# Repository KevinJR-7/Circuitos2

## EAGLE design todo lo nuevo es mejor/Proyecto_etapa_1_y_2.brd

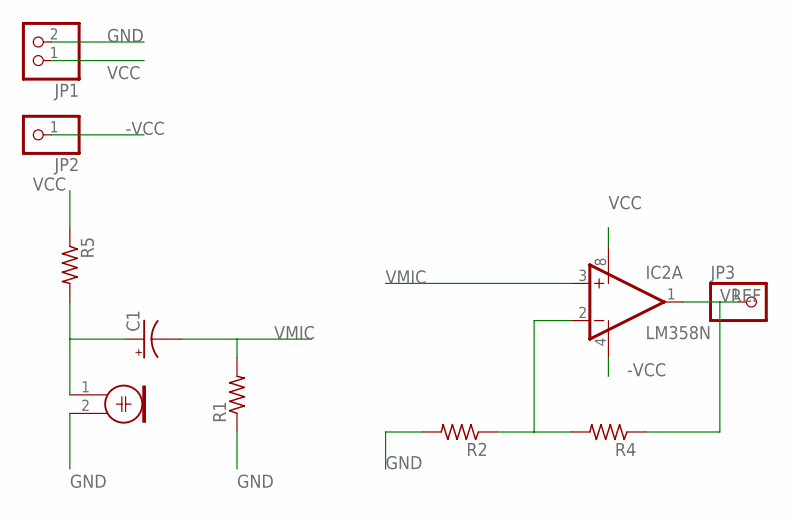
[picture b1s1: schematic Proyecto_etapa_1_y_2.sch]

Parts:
C1: CPOL-USE2.5-6; E2,5-6
IC2: LM358N; DIL08
JP1: PINHD-1X2; 1X02
JP2, JP3: PINHD-1X1; 1X01
M2: ELECTRET_MICROPHON-F6050AP; F6050AP
R1, R2, R4, R5: R-US_0207/10; 0207/10

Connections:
-VCC: IC2.4 (V-), JP2.1
GND: JP1.2, M2.2, R1.1, R2.2
unnamed: C1.+, M2.1, R5.2
unnamed: IC2.2 (-IN), R2.1, R4.2
VCC: IC2.8 (V+), JP1.1, R5.1
VMIC: C1.-, IC2.3 (+IN), R1.2
VREF: IC2.1 (OUT), JP3.1, R4.1

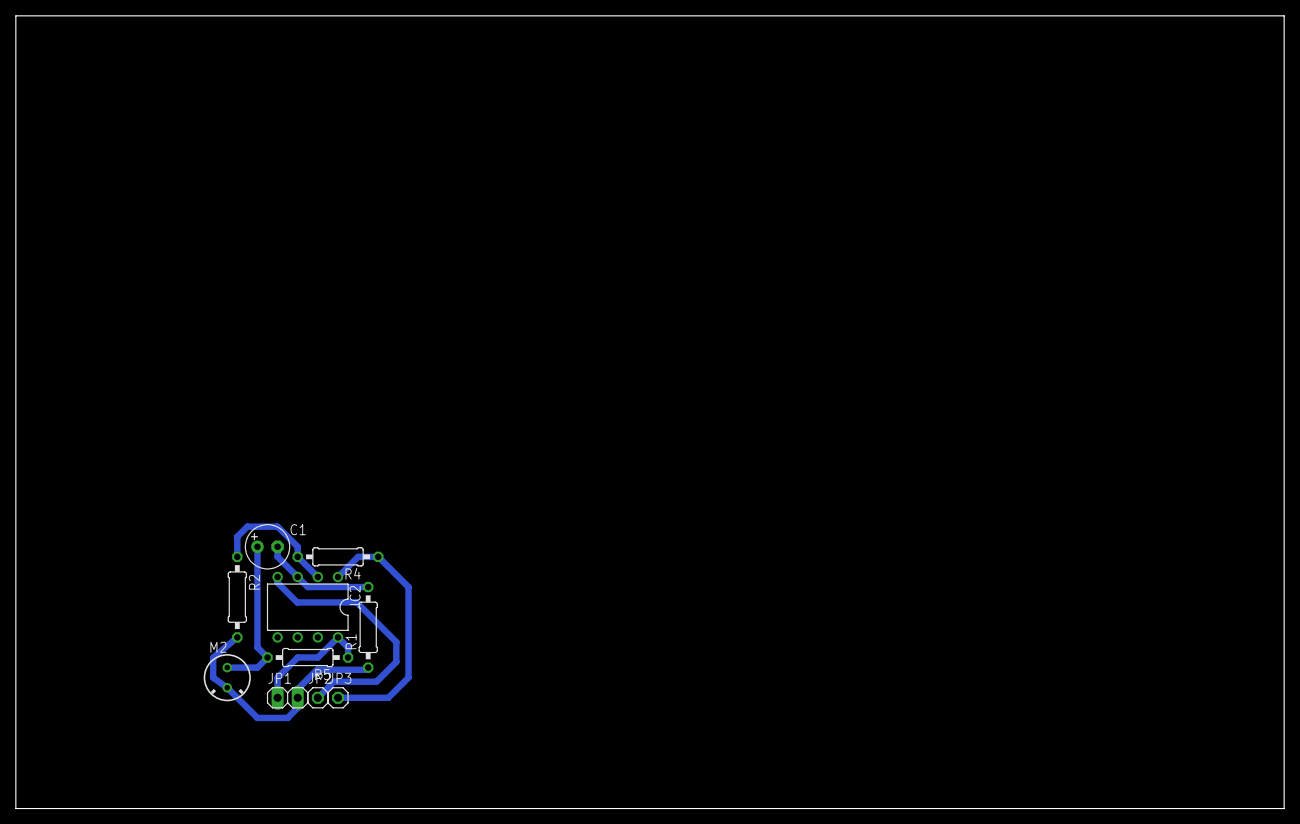
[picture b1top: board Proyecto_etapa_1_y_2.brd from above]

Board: 2 copper layers, 160.0 x 100.0 mm, 10 parts (0 on the bottom side), 7 nets.

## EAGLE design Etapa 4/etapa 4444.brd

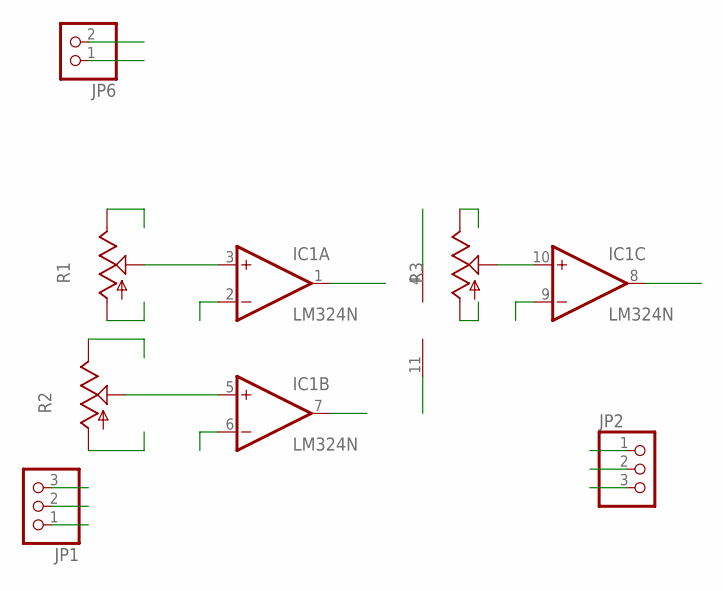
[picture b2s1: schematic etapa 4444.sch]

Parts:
IC1: LM324N; DIL14
JP1, JP2: PINHD-1X3; 1X03
JP6: PINHD-1X2; 1X02
R1, R2, R3: TRIM_US-S64W; S64W

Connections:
FIL1: IC1.2 (-IN), JP1.2
FIL2: IC1.6 (-IN), JP1.3
FIL3: IC1.9 (-IN), JP1.1
GND: IC1.11 (V-), JP6.1, R1.A, R2.A, R3.A
unnamed: IC1.5 (+IN), R2.S
unnamed: IC1.3 (+IN), R1.S
unnamed: IC1.10 (+IN), R3.S
OFIL1: IC1.1 (OUT), JP2.1
OFIL2: IC1.7 (OUT), JP2.2
OFIL3: IC1.8 (OUT), JP2.3
VCC: IC1.4 (V+), JP6.2, R1.E, R2.E, R3.E

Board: 2 copper layers, 7 parts (0 on the bottom side), 11 nets, no tracks yet.

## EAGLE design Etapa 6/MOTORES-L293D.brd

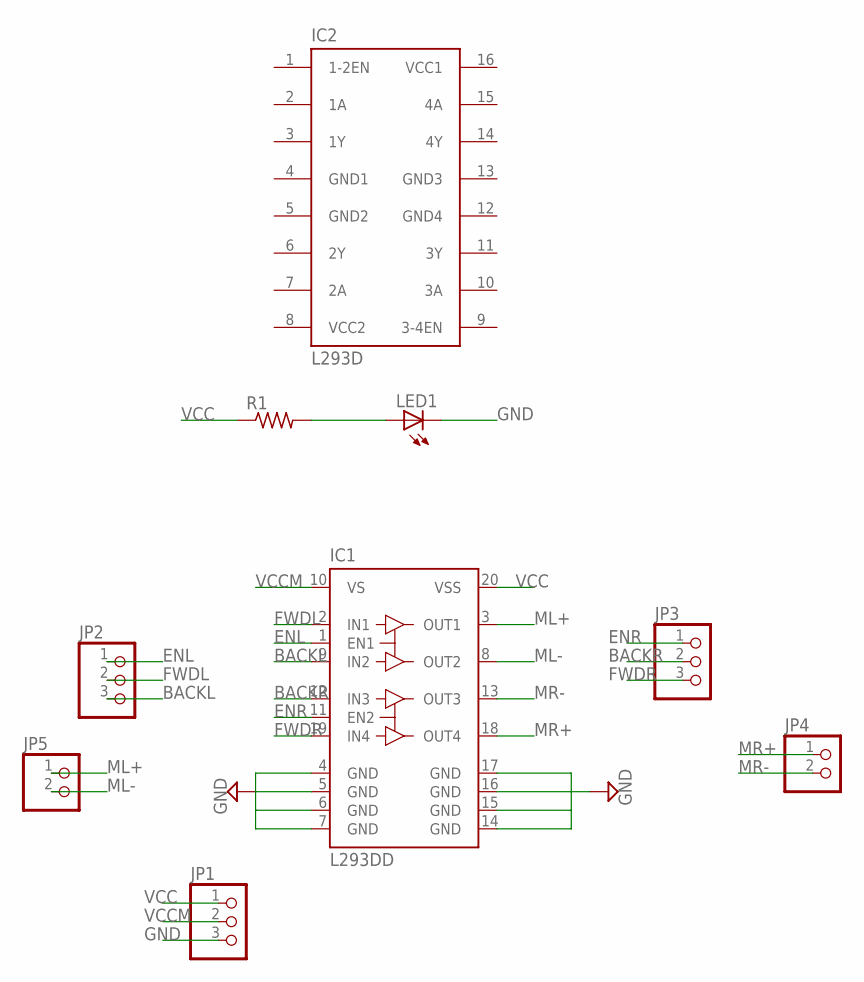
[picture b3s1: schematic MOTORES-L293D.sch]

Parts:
IC1: L293DD; SO20
IC2: L293D; DIL16
JP1, JP2, JP3: PINHD-1X3; 1X03
JP4, JP5: PINHD-1X2; 1X02
LED1: LED5MM
R1: R-US_R0603; R0603

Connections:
BACKL: IC1.9 (IN2), JP2.3
BACKR: IC1.12 (IN3), JP3.2
ENL: IC1.1 (EN1), JP2.1
ENR: IC1.11 (EN2), JP3.1
FWDL: IC1.2 (IN1), JP2.2
FWDR: IC1.19 (IN4), JP3.3
GND: IC1.4 (GND), IC1.5 (GND), IC1.6 (GND), IC1.7 (GND), IC1.14 (GND), IC1.15 (GND), IC1.16 (GND), IC1.17 (GND), JP1.3, LED1.K (C)
GND1: IC2.4 (GND1)
GND2: IC2.5 (GND2)
GND3: IC2.13 (GND3)
GND4: IC2.12 (GND4)
ML+: IC1.3 (OUT1), JP5.1
ML-: IC1.8 (OUT2), JP5.2
MR+: IC1.18 (OUT4), JP4.1
MR-: IC1.13 (OUT3), JP4.2
unnamed: LED1.A, R1.2
VCC: IC1.20 (VSS), JP1.1, R1.1
VCC1: IC2.16 (VCC1)
VCC2: IC2.8 (VCC2)
VCCM: IC1.10 (VS), JP1.2

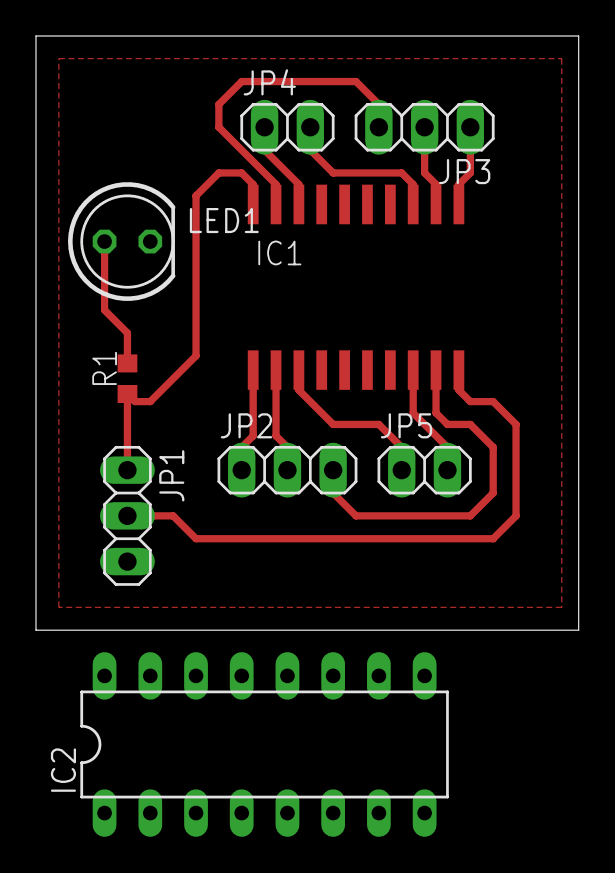
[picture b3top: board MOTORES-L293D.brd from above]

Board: 2 copper layers, 30.1 x 33.0 mm, 9 parts (0 on the bottom side), 14 nets.

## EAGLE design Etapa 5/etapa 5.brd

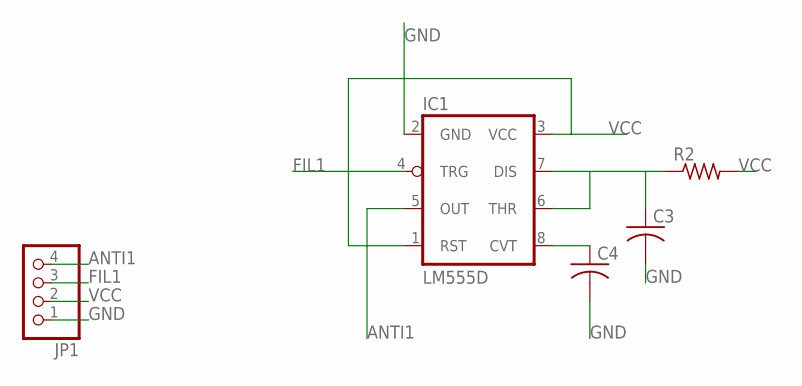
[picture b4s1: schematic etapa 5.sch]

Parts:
C3, C4: C-USC0603; C0603
IC1: LM555D; SO08
JP1: PINHD-1X4; 1X04
R2: R-US_R0603; R0603

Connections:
ANTI1: IC1.5 (OUT), JP1.4
FIL1: IC1.4 (TRG), JP1.3
GND: C3.2, C4.2, IC1.2 (GND), JP1.1
unnamed: C4.1, IC1.8 (CVT)
unnamed: C3.1, IC1.6 (THR), IC1.7 (DIS), R2.1
VCC: IC1.1 (RST), IC1.3 (VCC), JP1.2, R2.2

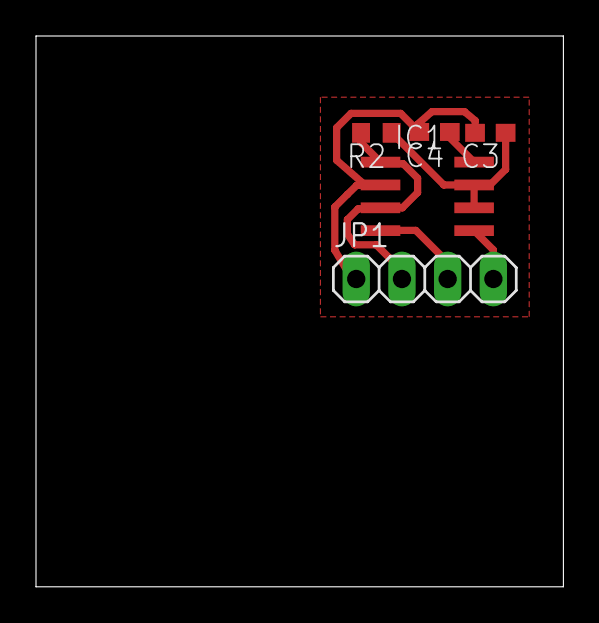
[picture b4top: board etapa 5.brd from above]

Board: 2 copper layers, 29.3 x 30.6 mm, 5 parts (0 on the bottom side), 6 nets.

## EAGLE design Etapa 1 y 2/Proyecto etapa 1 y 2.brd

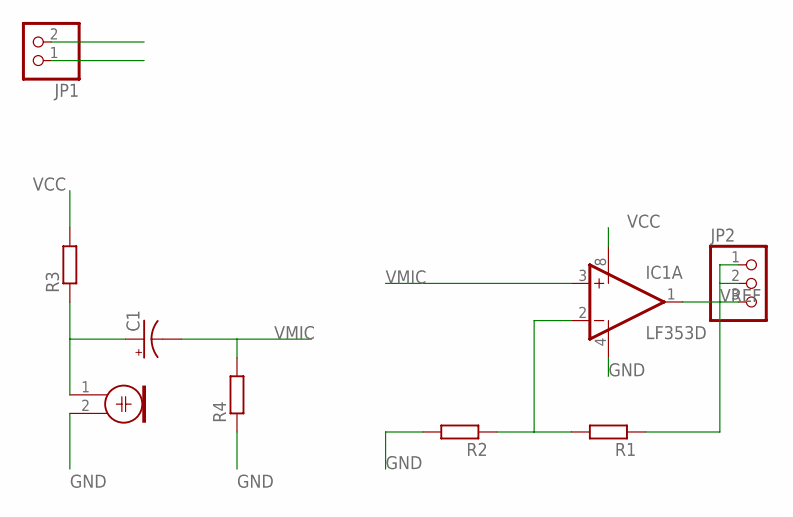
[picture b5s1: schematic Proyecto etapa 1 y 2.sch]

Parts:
C1: CPOL-USC/6032-28R; C/6032-28R
IC1: LF353D; SO08
JP1: PINHD-1X2; 1X02
JP2: PINHD-1X3; 1X03
M1: ELECTRET_MICROPHON-WM-62PC/62PK; WM-62PC/62PK
R1, R2, R3, R4: R-EU_R0603; R0603

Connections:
GND: IC1.4 (V-), JP1.2, M1.2, R2.2, R4.1
unnamed: C1.+, M1.1, R3.1
unnamed: IC1.2 (-IN), R1.2, R2.1
VCC: IC1.8 (V+), JP1.1, R3.2
VMIC: C1.-, IC1.3 (+IN), R4.2
VREF: IC1.1 (OUT), JP2.1, JP2.2, JP2.3, R1.1

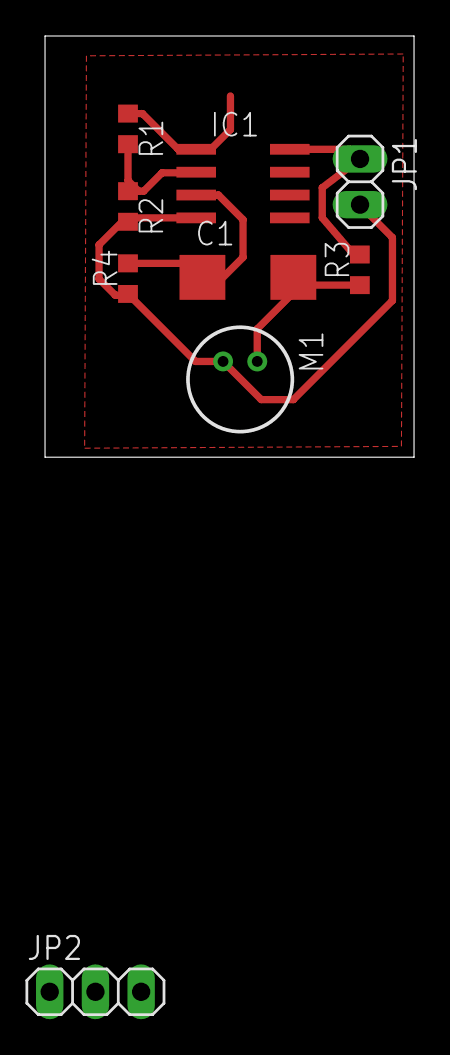
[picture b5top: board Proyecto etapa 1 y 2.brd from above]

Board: 2 copper layers, 20.5 x 23.4 mm, 9 parts (0 on the bottom side), 6 nets.

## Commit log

2024-07-16 Final
